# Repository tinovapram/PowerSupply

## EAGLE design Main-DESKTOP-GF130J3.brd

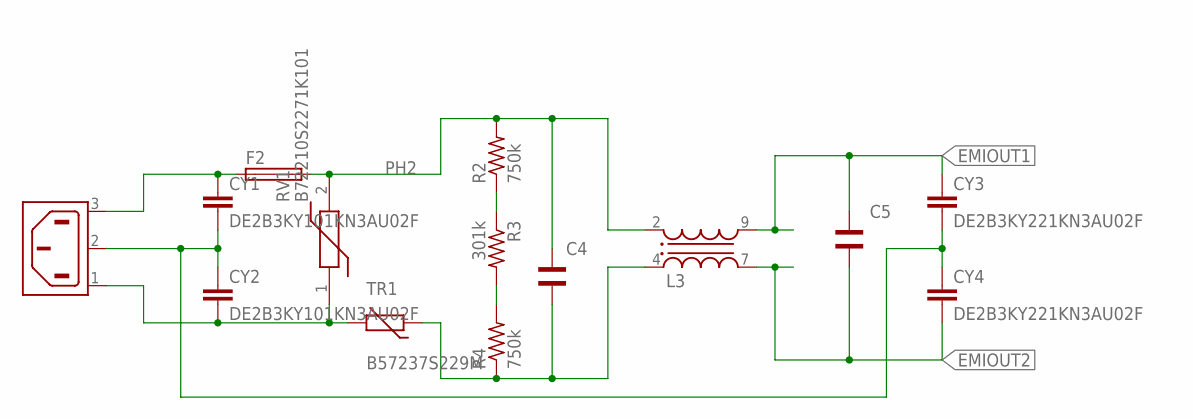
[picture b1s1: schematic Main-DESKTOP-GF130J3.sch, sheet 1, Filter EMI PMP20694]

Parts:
C4, C5: WCAP-FTXX_890334025039CS; WCAP-FTXX_15X18X14X8
CY1, CY2: DE2B3KY101KN3AU02F; YC7B5
CY3, CY4: DE2B3KY221KN3AU02F; YC7B5
F2: GSH15
L3: WE-CMB_L_744824310; WE-CMB_L
R2, R4: 750k; R1206
R3: 301k; R1206
RV1: B72210S2271K101
TR1: B57237S229M; R-7,5
X1: 6ESRM-P

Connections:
EMIOUT1: C5.2, CY3.1, L3.9 (3); also elsewhere on the board
EMIOUT2: C5.1, CY4.2, L3.7 (2); also elsewhere on the board
unnamed: R2.1, R3.1
unnamed: R3.2, R4.2
unnamed: CY1.1, F2.1, X1.3 (AC2)
unnamed: CY2.2, RV1.1, TR1.2, X1.1 (AC1)
unnamed: C4.2, L3.4 (1), R4.1, TR1.1
unnamed: CY1.2, CY2.1, CY3.2, CY4.1, X1.2 (SH)
PH2: C4.1, F2.2, L3.2 (4), R2.2, RV1.2

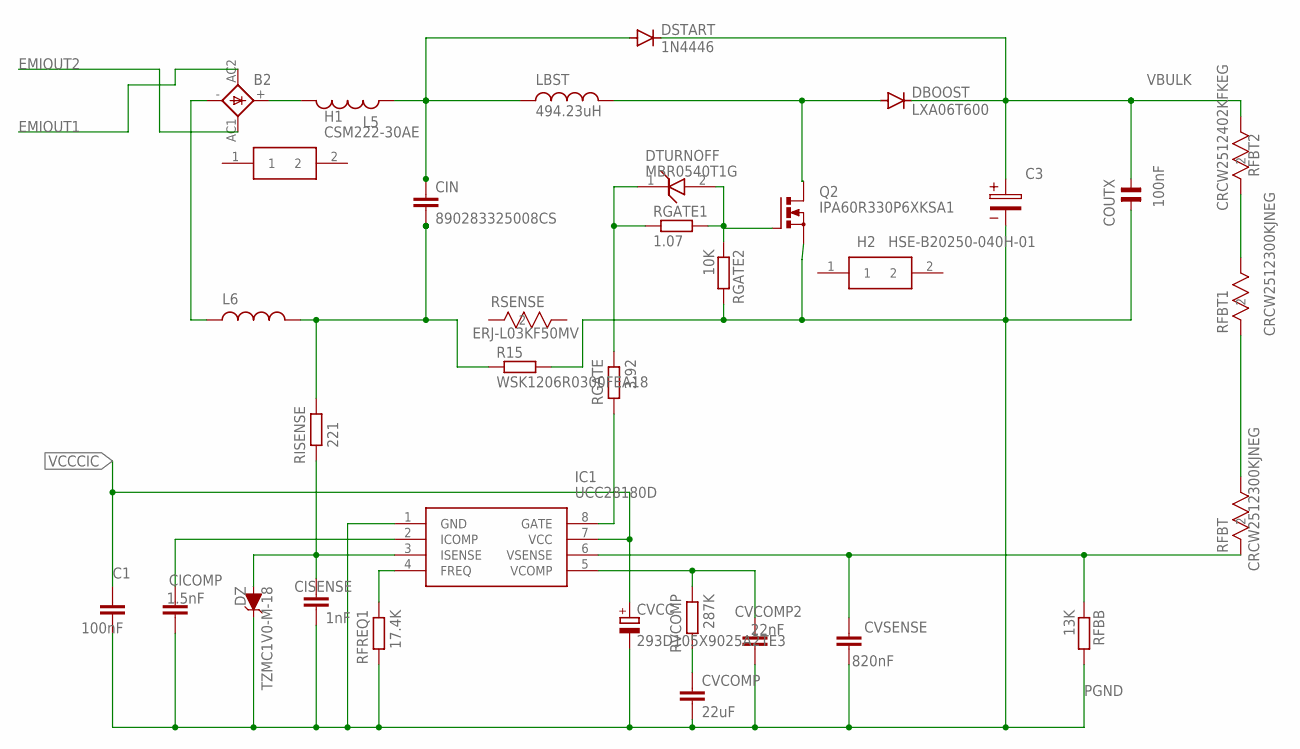
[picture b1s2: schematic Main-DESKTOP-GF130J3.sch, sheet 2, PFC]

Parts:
B2: GBU4; GBU4S
C1: 100nF; C0603
C3: WCAP-AIG8_30X46_861011485018; 30X10X2(DXPXΦ)
CICOMP: 1.5nF; C0603K
CIN: 890283325008CS; C150-072X183
CISENSE: 1nF; C0402
COUTX: 100nF; C10,0-14,0X6,0
CVCC: 293D105X9025A2TE3; CT3216
CVCOMP: 22uF; C0805
CVCOMP2: 22nF; C0603K
CVSENSE: 820nF; C0805
DBOOST: LXA06T600; TO220ACS
DSTART: 1N4446; DO35-10
DTURNOFF: MBR0540T1G; SOD3716X135N
DZ: TZMC1V0-M-18; DIOMELF3515
H1: CSM222-30AE; CSM22230AE
H2: HSE-B20250-040H-01; HSEB20250040H01
IC1: UCC28180D; SOIC127P600X175-8N
L5, L6: WE-FI_7447016
LBST: 494.23uH; WE-SI_744139
Q2: IPA60R330P6XKSA1; TO220BV
R15: WSK1206R0300FEA18; R3216
RFBB: 13K; R0603
RFBT, RFBT1: CRCW2512300KJNEG; RC2512N
RFBT2: CRCW2512402KFKEG; RC2512N
RFREQ1: 17.4K; R0603
RGATE: 3.92; R0603
RGATE1: 1.07; R0603
RGATE2: 10K; R0603
RISENSE: 221; R0603
RSENSE: ERJ-L03KF50MV; RC0603N
RVCOMP: 287K; R0603

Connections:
EMIOUT1: B2.AC2 (AC1); also elsewhere on the board
EMIOUT2: B2.AC1 (AC2); also elsewhere on the board
GATE: IC1.8 (GATE), RGATE.2
unnamed: B2.-, L6.1
unnamed: CIN.2, L6.2, R15.1, RISENSE.1
unnamed: DBOOST.A, LBST.2, Q2.D
unnamed: B2.+, L5.2
unnamed: CIN.1, DSTART.A, L5.1, LBST.1
unnamed: DTURNOFF.2 (A), Q2.G, RGATE1.2, RGATE2.1
unnamed: DTURNOFF.1 (K), RGATE.1, RGATE1.1
unnamed: CVCOMP.1, RVCOMP.2
unnamed: RFBT1.1, RFBT2.2
unnamed: RFBT.1, RFBT1.2
N$FREQ: IC1.4 (FREQ), RFREQ1.1
N$ICOMP: CICOMP.2, IC1.2 (ICOMP)
N$ISENSE: CISENSE.1, DZ.1 (A), IC1.3 (ISENSE), RISENSE.2
N$VCOMP: CVCOMP2.2, IC1.5 (VCOMP), RVCOMP.1
N$VSENSE: CVSENSE.2, IC1.6 (VSENSE), RFBB.1, RFBT.2
PGND: C1.2, C3.2, CICOMP.1, CISENSE.2, COUTX.2, CVCC.-, CVCOMP.2, CVCOMP2.1, CVSENSE.1, DZ.2 (C), IC1.1 (GND), Q2.S, R15.2, RFBB.2, RFREQ1.2, RGATE2.2; also elsewhere on the board
VBULK: C3.1, COUTX.1, DBOOST.C, DSTART.C, RFBT2.1; also elsewhere on the board
VCCCIC: C1.1, CVCC.+, IC1.7 (VCC); also elsewhere on the board

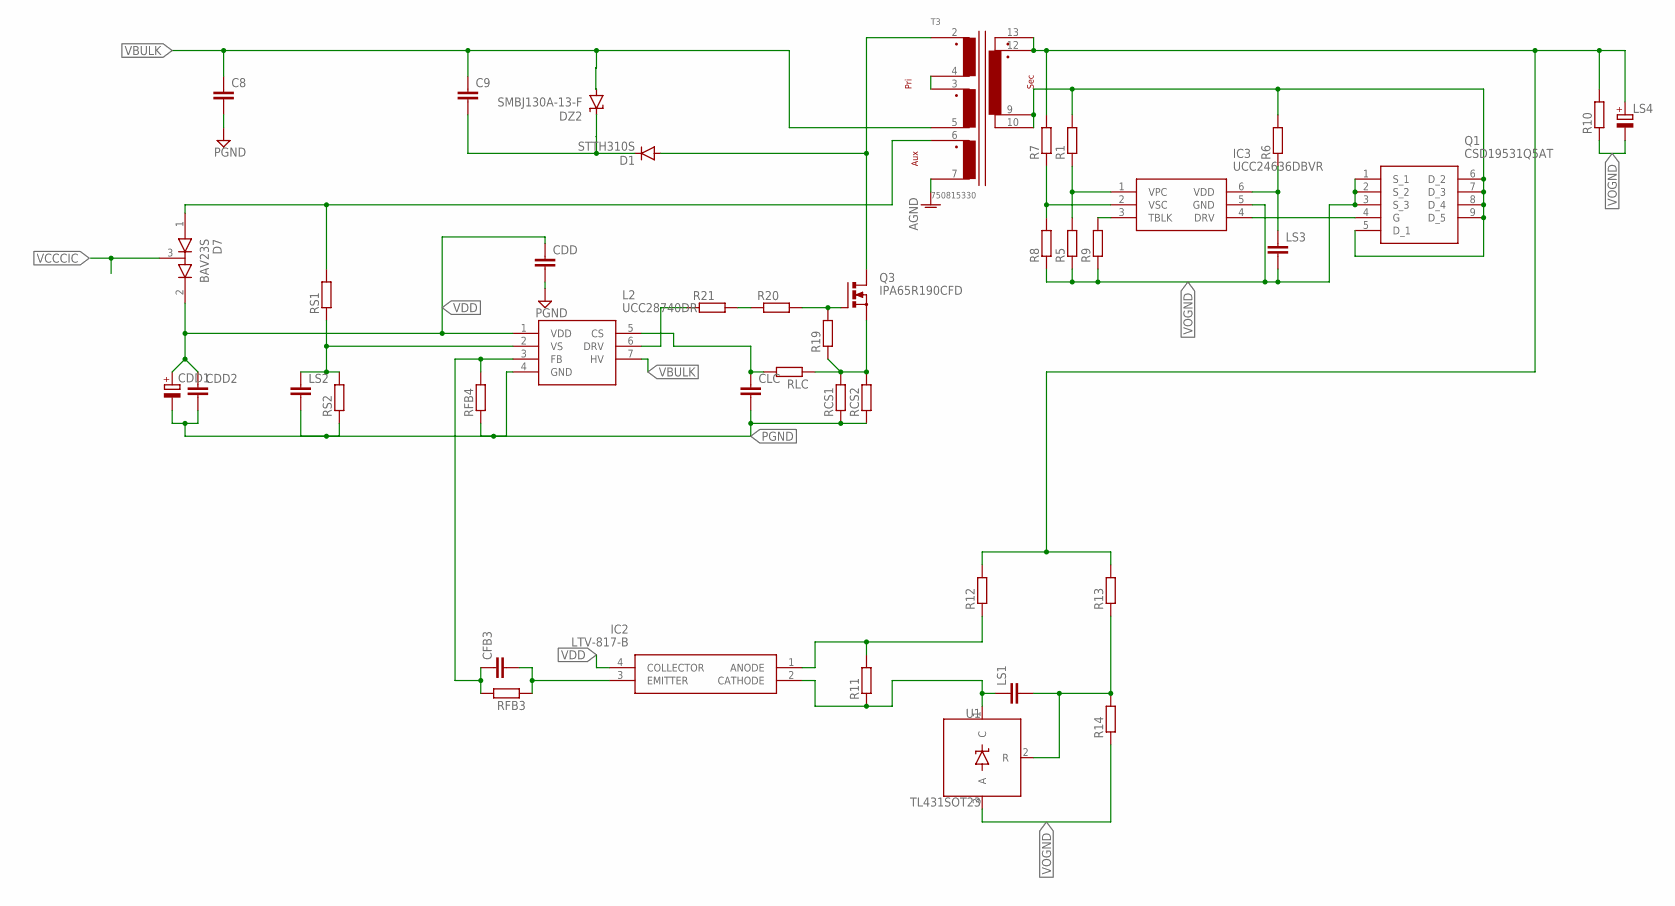
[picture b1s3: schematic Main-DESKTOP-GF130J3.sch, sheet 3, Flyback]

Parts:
C8, C9: C-EUC0805; C0805
CDD, CDD2: C-EUC0805; C0805
CDD1: CPOL-EUTT2D5; TT2D5
CFB3: C-EUC0805; C0805
CLC: C-EUC0805; C0805
D1: STTH310S; SMC
D7: BAV23S; SOT95P230X110-3N
DZ2: SMBJ130A-13-F; SMBJ
IC2: LTV-817-B; DIP762W60P254L460H420Q4N
IC3: UCC24636DBVR; SOT95P280X145-6N
L2: UCC28740DR; D(R-PDSO-G7)
LS1, LS2, LS3: C-EUC0805; C0805
LS4: CPOL-EU153CLV-1010; 153CLV-1010
Q1: CSD19531Q5AT
Q3: IPA65R190CFD; TO220BV
R1, R5, R6, R7, R8, R9, R10, R11, R12, R13, R14, R19, R20, R21: R-EU_R0805; R0805
RCS1, RCS2: R-EU_R0805; R0805
RFB3, RFB4: R-EU_R0805; R0805
RLC: R-EU_R0805; R0805
RS1, RS2: R-EU_R0805; R0805
T3: 750815330; EE25/13/7_THT_H_14PIN_(5644)
U1: TL431SOT23; SOT23-3

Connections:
unnamed 7: LS1.2, R13.1, R14.2, U1.2 (R); also elsewhere on the board
unnamed: CFB3.2, IC2.3 (EMITTER), RFB3.1
unnamed: T3.3, T3.4
unnamed: D7.1, RS1.2, T3.6
unnamed 14: IC2.1 (ANODE), R11.2, R12.1; also elsewhere on the board
unnamed: CFB3.1, L2.3 (FB), RFB3.2, RFB4.2
unnamed 17: IC2.2 (CATHODE), LS1.1, R11.1, U1.1 (C); also elsewhere on the board
unnamed 18: LS4.+, R7.2, R10.2, R12.2, R13.2, T3.12, T3.13; also elsewhere on the board
unnamed: IC3.4 (DRV), Q1.4 (G)
unnamed: L2.2 (VS), LS2.1, RS1.1, RS2.2
unnamed: Q1.5 (D_1), Q1.6 (D_2), Q1.7 (D_3), Q1.8 (D_4), Q1.9 (D_5), R1.2, R6.2, T3.9, T3.10
unnamed: R20.1, R21.2
unnamed: Q3.G, R19.2, R20.2
unnamed: C9.2, D1.C, DZ2.C
unnamed: D1.A, Q3.D, T3.2
N$CS: CLC.1, L2.5 (CS), RLC.2
N$DRV: L2.6 (DRV), R21.1
N$TBK: IC3.3 (TBLK), R9.2
N$VODD: IC3.6 (VDD), LS3.1, R6.1
N$VPC: IC3.1 (VPC), R1.1, R5.2
N$VSC: IC3.2 (VSC), R7.1, R8.2
PGND: C8.2, CDD.2, CDD1.-, CDD2.2, CLC.2, L2.4 (GND), LS2.2, RCS1.1, RCS2.1, RFB4.1, RS2.1, T3.7; also elsewhere on the board
TOISENSE: Q3.S, R19.1, RCS1.2, RCS2.2, RLC.1
VBULK: C8.1, C9.1, DZ2.A, L2.7 (HV), T3.5; also elsewhere on the board
VCCCIC: D7.3; also elsewhere on the board
VDD: CDD.1, CDD1.+, CDD2.1, D7.2, IC2.4 (COLLECTOR), L2.1 (VDD)
VOGND: IC3.5 (GND), LS3.2, LS4.-, Q1.1 (S_1), Q1.2 (S_2), Q1.3 (S_3), R5.1, R8.1, R9.1, R10.1, R14.1, U1.3 (A); also elsewhere on the board

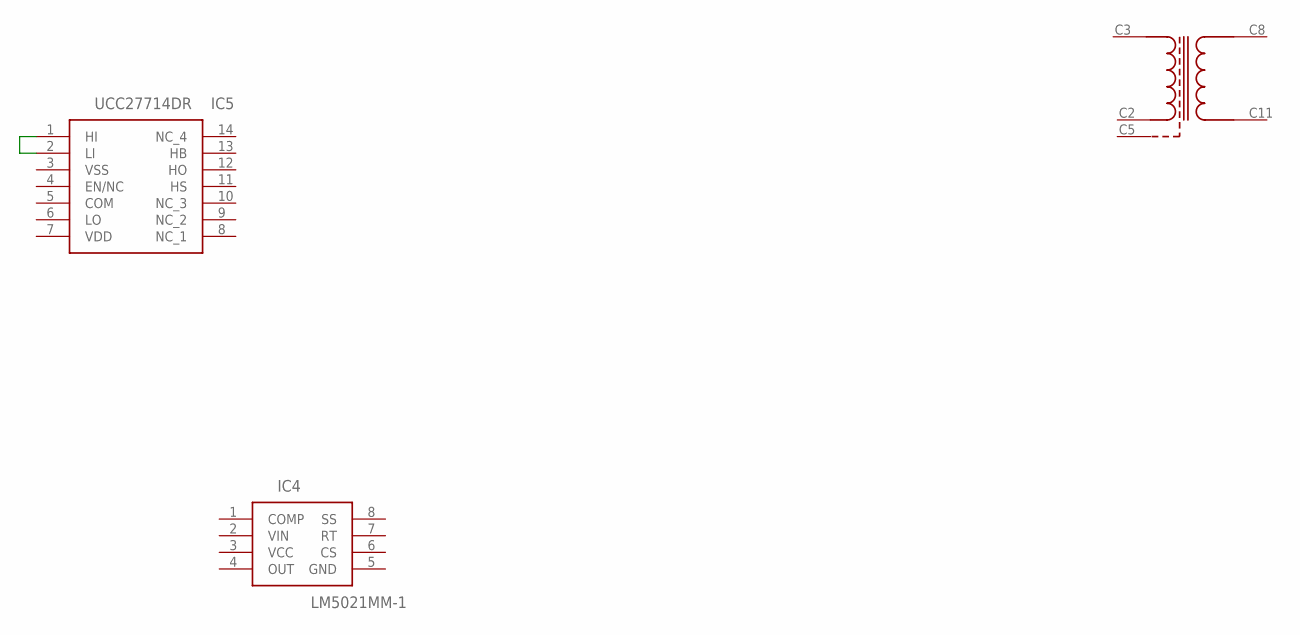
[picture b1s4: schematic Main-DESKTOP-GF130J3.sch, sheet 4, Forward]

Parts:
IC4: LM5021MM-1; SOP65P490X110-8N
IC5: UCC27714DR; SOIC127P600X175-14N
T2: 750315800; PQ3230

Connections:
unnamed: IC5.1 (HI), IC5.2 (LI)

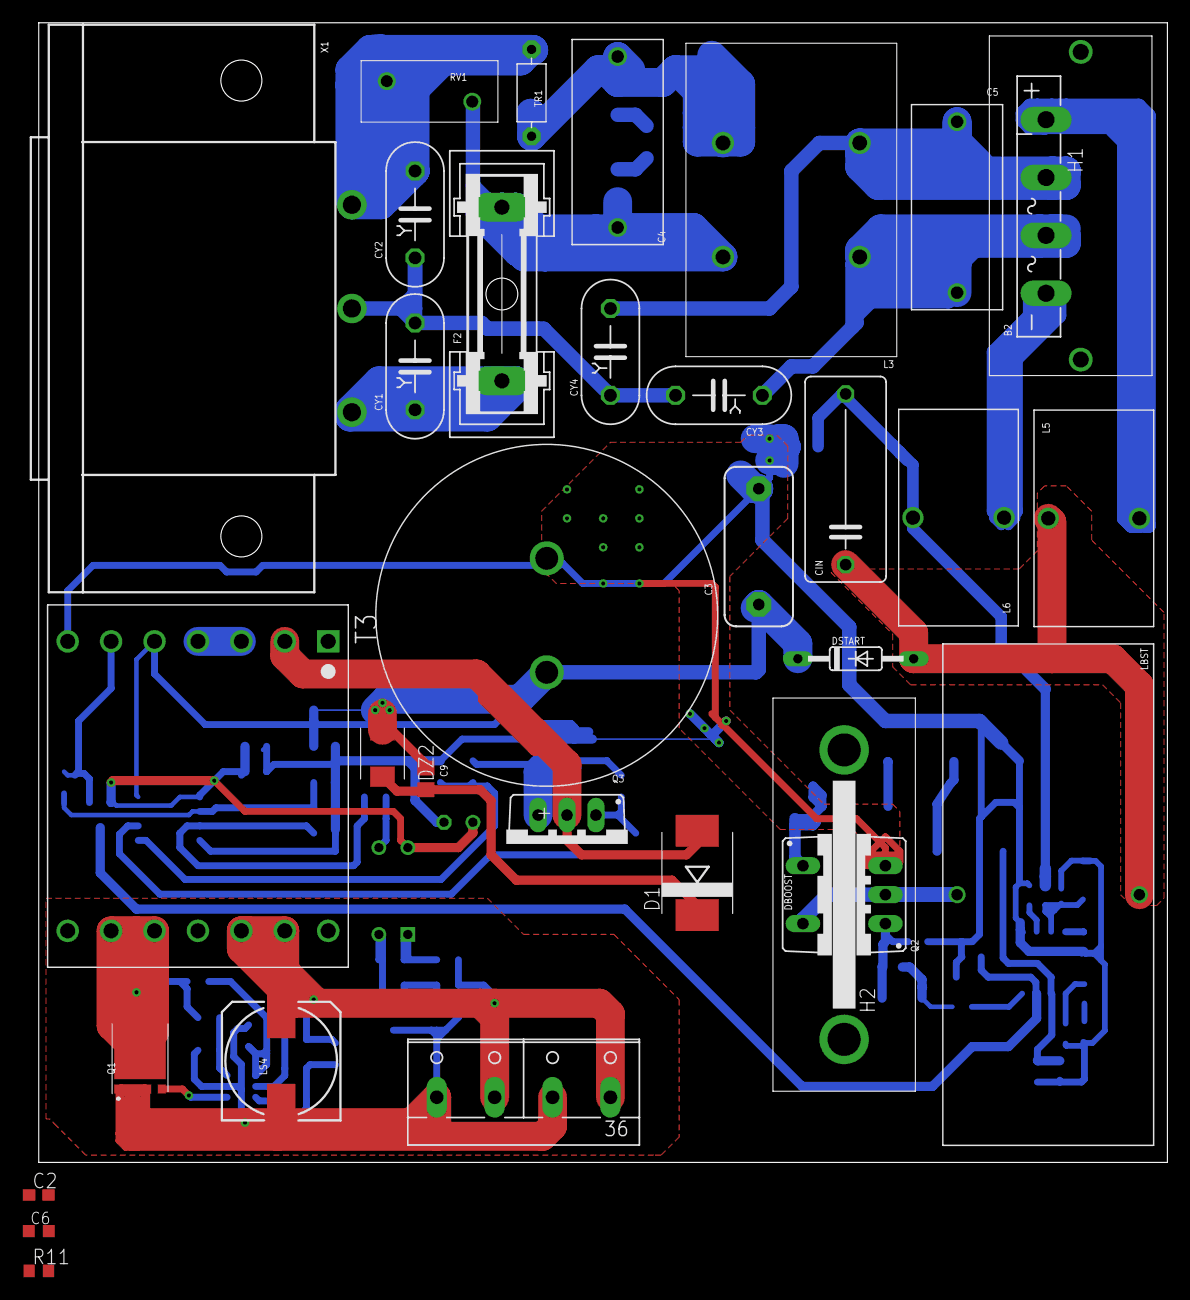
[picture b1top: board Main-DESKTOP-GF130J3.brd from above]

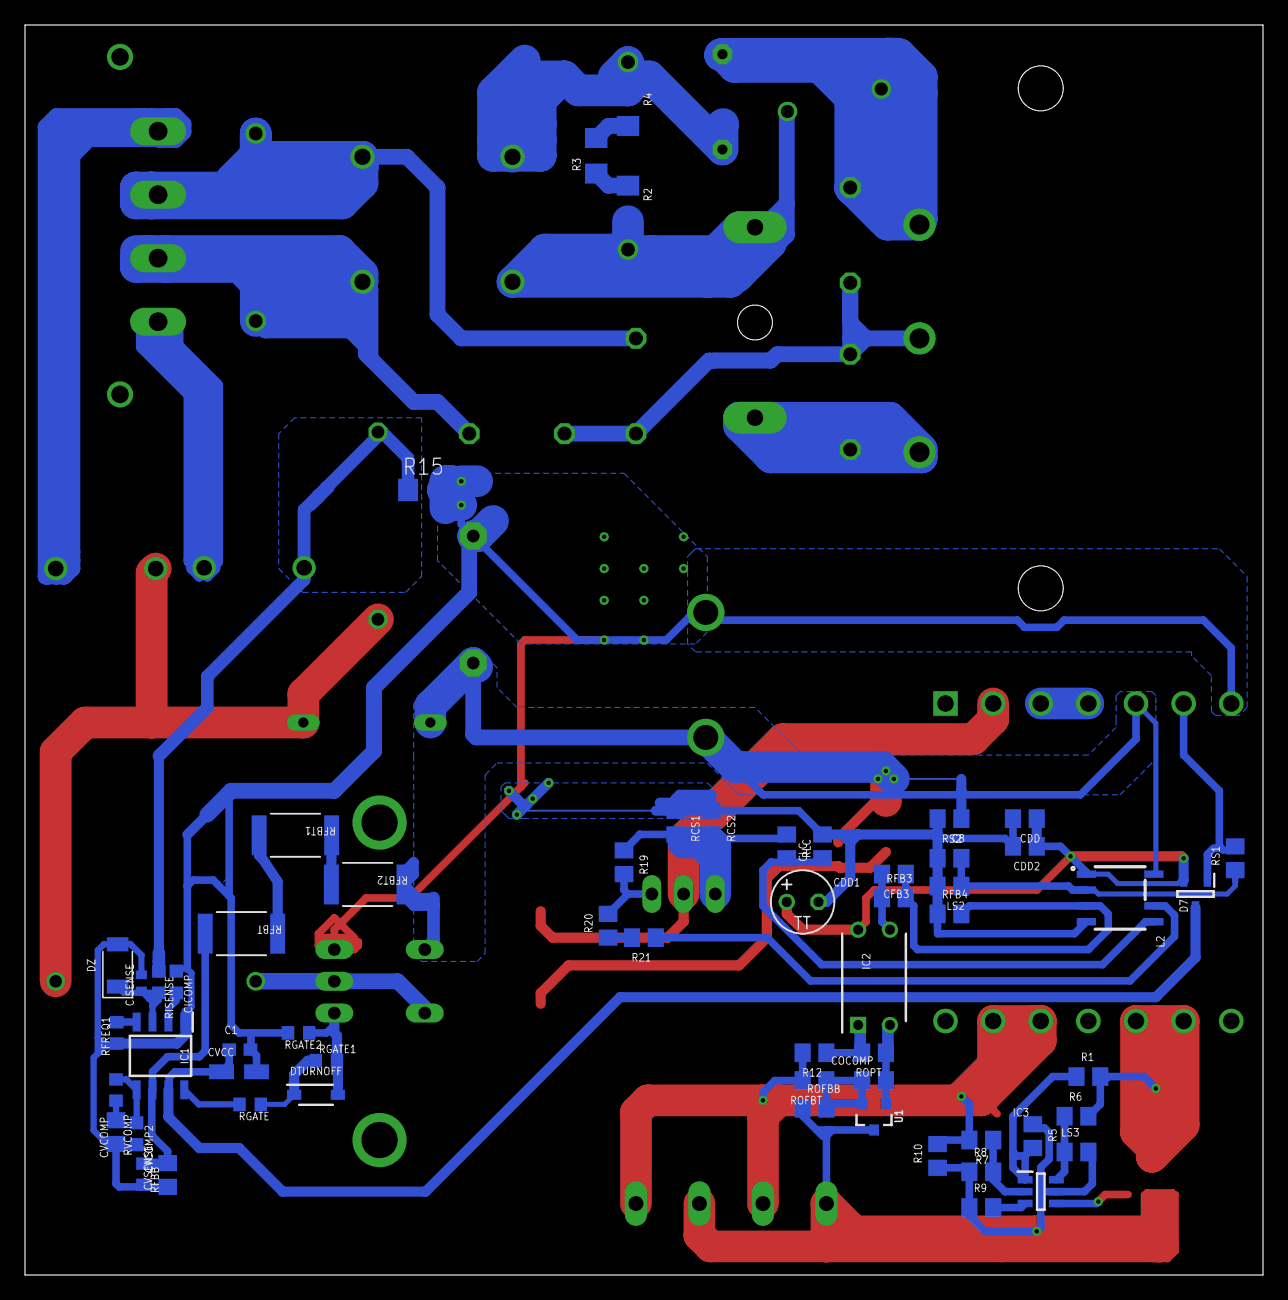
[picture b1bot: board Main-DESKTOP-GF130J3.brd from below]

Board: 2 copper layers, 99.0 x 100.0 mm, 93 parts (59 on the bottom side), 52 nets.

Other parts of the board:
36: +36; W237-4P
C2: C0603
C6: C0603K
COCOMP: C0805
ROFBB: R0805
ROFBT: R0805
ROPT: R0805

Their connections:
unnamed 7: COCOMP.2, ROFBB.2, ROFBT.1; also elsewhere on the board
unnamed 14: ROPT.2; also elsewhere on the board
unnamed 17: COCOMP.1, ROPT.1; also elsewhere on the board
unnamed 18: 36.2, 36.4, ROFBT.2; also elsewhere on the board
VOGND: 36.1, 36.3, ROFBB.1; also elsewhere on the board

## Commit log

2019-07-05 Fix Cap Size v1
2019-07-05 Cav Size v2
2019-07-09 090719
2019-07-12 12 Juli 2019
2019-07-19 19 Juli

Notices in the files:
parts and their libraries:
Wurth_Elektronik_Passive_rev18f: Copyright: Würth Elektronik
wurth_electronics_midcom_inc_v2-1: Copyright: Wurth Electronics Midcom, Inc.
SparkFun-DiscreteSemi: Licensing: Creative Commons ShareAlike 4.0 International - https://creativecommons.org/licenses/by-sa/4.0
